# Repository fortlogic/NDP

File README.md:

# [NDP][]

Thanks for starting a project with Haskeleton! If you haven't heard of it
before, I suggest reading the introductory blog post. You can find it here:
<http://taylor.fausak.me/2014/03/04/haskeleton-a-haskell-project-skeleton/>.

Before you get started, there are a few things that this template couldn't
provide for you. You should:

-   Add a synopsis to `package.yaml`. It should be a short (one sentence)
    explanation of your project.

-   Add a description to `package.yaml`. This can be whatever you want it to
    be.

-   Add a category to `package.yaml`. A list of categories is available on
    Hackage at <http://hackage.haskell.org/packages>.

-   Rename `library/Example.hs` to whatever you want your top-level module to
    be called. Typically this is the same as your package name but in
    `CamelCase` instead of `kebab-case`.

    -   Don't forget to rename the reference to it in
        `executable/Main.hs`!

-   If you are on an older version of Stack (<1.0.4), delete `package.yaml` and
    remove `/*.cabal` from your `.gitignore`.

Once you've done that, start working on your project with the Stack commands
you know and love.

``` sh
# Build the project.
stack build

# Run the test suite.
stack test

# Run the benchmarks.
stack bench

# Generate documentation.
stack haddock
```

Thanks again, and happy hacking!

[NDP]: https://github.com/githubuser/NDP

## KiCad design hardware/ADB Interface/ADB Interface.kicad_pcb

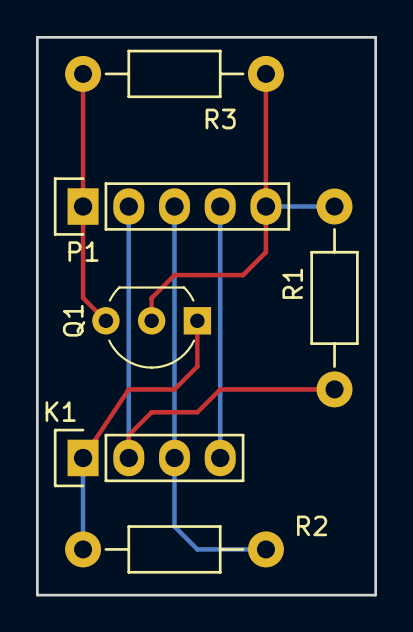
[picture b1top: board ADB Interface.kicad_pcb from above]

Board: 2 copper layers, 18.8 x 31.0 mm, 6 parts (0 on the bottom side), 6 nets.

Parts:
K1: ADB; Socket_Strip_Straight_1x04
P1: CONN_01X05; Socket_Strip_Straight_1x05
Q1: ZVNL110A; TO-92_Inline_Wide
R1, R2, R3: 470; Resistor_Horizontal_RM10mm

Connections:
+3V3: P1.5, Q1.2, R1.1, R3.2
+5V: K1.3, P1.3, R2.2
/adb: P1.1, Q1.3, R3.1
/~poweron: K1.2, P1.2, R1.2
GND: K1.4, P1.4
unnamed: K1.1, Q1.1, R2.1

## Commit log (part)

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2016-09-23 Initial commit.
2016-09-23 Fixed TileROM.hs from writing inverted tiles into a ROM.
2016-09-24 Update cbm tileset to include all letters.
2016-09-28 Refactored build system.
2016-09-29 basic testing framework setup.
2016-09-29 Started TMDS encoder.
2016-10-02 Research folder contains papers and articles that I don't have the rights to post publicly. I might commit a list with titles and links if someone else wants them.
2016-10-02 TMDS data encoding complete, testing and control codes still unfinished.
2016-10-02 All but the reference TMDS tests fail.
2016-10-02 x(n)or encoding and decoding functions properly.
2016-10-03 Finished TMDS encoding.
2016-10-04 Fixed some language declarations, added some interesting bit shuffling routines.
2016-10-04 Reorganisation in progress.
2016-10-04 Make system builds.
2016-10-04 Reorganisation finished, tests work fine.
2016-10-04 Restructuring clash compilation to handle nested modules.
2016-10-05 Started writing timing code. I hate election season.
2016-10-05 Added arrow instance for signals. Some arrow laws have been shown to be correct, others will be proven when time permits.
2016-10-06 Changed some names, added some module exports, added C64 inspired colour palette.
2016-10-06 Modified TMDS to be a little more friendly, begun work on video signal generator, and defined some initial clock domains.
2016-10-06 RGB video generator theoretically works, needs to be hooked up to a serialiser.
2016-10-06 Renamed video generator, started using proper clock domains for pixel logic.
2016-10-07 Started putting together the pieces to form the HDMI signal generator.
2016-10-08 HDMI generator should theoretically be capable of synthesising a test image. Still need to hook it up to ODDR output elements and test it on the actual fpga first.
2016-10-08 copied over a vagrant file from another project.
2016-10-09 Teaching the build system about vagrant.
2016-10-09 withVagrant fails if the vagrant status oracle cannot startup the vm.
2016-10-10 Added oracle for CPU architecture.
2016-10-12 Build system is a little stricter in terms of what CLaSH files can be compiled into vhdl, but output is not properly segregated into separate containers.
2016-10-12 Added the default constraints file for the Pipstrello (v2) board.
2016-10-16 can build ghdl test benches.
2016-10-18 Correctly builds project file for the xilinx toolchain.
2016-10-22 Renamed research folder to reference, added ISE folder for storing Xilinx ISE project in a location that git won't track.
2016-10-22 Begun refactoring.
2016-10-22 Added bit file compilation.
2016-10-22 Finished refactor.
2016-11-02 Xilinx bit file generation seems to work.
2016-11-02 Added minimal vhdl DVI-D output test (from the lovely hamster works).
2016-11-02 Copied minimal dvi-d demo in preparation for integrating the TMDS encoder.
2016-11-02 cleanup.
2016-11-05 Fixed unnecessary recompilation of clash sources.
2016-11-05 tmds encoder test entity fully replicates the functionality of the minimal dvid test entity.
2016-11-08 tmds sort of works? the tv says ‘no signal’ most of the time but every few minutes displays several correct frames before the signal goes invalid again.
2016-11-08 Started separating top level (phony) targets into their own file.
2016-11-13 Rewrite encodeByte. TMDS encoding now works, MinimalDVIDPlusTMDS also works.
2017-01-04 Updated the tilemap to look prettier (unified the character weight).
2017-01-08 Made an ADB schematic and PCB layout.
    No idea if it’ll work. ;)
2017-01-08 Updated .gitignore.
2017-03-16 Futzed around with the hardware schematic.
2017-03-16 Started trying to implement an ADB bus.
2017-04-22 Updated to build with GHC-8.
2017-04-22 Project builds successfully.
2017-04-22 Bitfile for the HDMI test now builds successfully.
2017-05-05 Fixed various configuration bugs in the build system. Also started adding fpga related shortcuts to the build system.
2017-05-15 Added more shortcuts.
2017-05-15 Made constraint building (hopefully) more flexible.
2017-05-16 Added a top level fpga demo where all of the vhdl (aside from a small generic clock entity), and specifically the top level entity, is written entirely in Clash.
2017-05-16 stuff
2017-05-20 Added a vhdl package for talking to an SD card.
2017-05-20 Some cleanup.
2017-05-20 SDCard.vhdl works correctly in the xilinx ISE.
2017-05-20 Added SD card constraints.
2017-06-06 Created an SD card controller primitive that clash and the xilinx tools correctly synthesise.
2017-06-07 Made some changes in efforts to make it work with a real SD card. (hint: it doesn’t).
2018-03-27 Begun writing ALU
2018-03-27 Fixing build config.
2018-03-27 ALU faults are a thing.
    Once we have some
2018-04-02 Working on the ALU
2018-04-02 Restructured the ALU result type
2018-04-03 Added netlist ‘busses’
    specifying constraints is somewhat less horrific.
2018-04-05 Added wing A to constraints
    Right now it’s as a pullup. In the future the I/Oness and pullness of wing busses is something that should be specified in a designs Config.hs.
2018-04-06 Added other wings as constraints
2018-04-08 Added popcount ALU instruction
2018-04-08 Added some dependencies.
2018-04-08 Added PopCount test
2018-04-08 deleted cabal file
2018-04-10 Updated cabal deps
2018-04-10 Added PopCount vhdl entity
2018-04-10 Begun generalising HDL generation
    Start of support for more than just VHDL.
2018-04-10 Added verilog support
    breaks bitfile generation
2018-04-10 presence of XILINXROOT is now optional
2018-04-10 unbroke bitfile generation
2018-04-11 can now build fpga bitfiles from verilog
    yay!
2018-04-11 But I prefer vhdl :3
2018-04-23 Started thinking about how registers should work
2018-04-23 Royally fu… I mean moving stuff about.
2018-04-24 everything in `hardware/` seems to build…
2018-04-24 Everything builds
    But does it work? ;)
2018-04-24 We need a readme
    Right now it’s just TODOs, but we’ve got to start somewhere?
2018-04-24 Made Clash generation less crap.
2018-04-24 Added a todo
2018-04-24 Things mostly build
    Tests are still broken I think.
2018-04-24 Tests work
2018-04-24 Tests run
    oh god so many warnings.
2018-04-24 building stuff works again
    except for bitfiles :p
2018-04-24 Bitfile generation works
2018-04-24 forgot to depend on clash-ghc 😳
2018-04-24 Added fpga stage command
2018-04-25 bumped resolver
2018-04-25 Got Hamster’s Minimal DVID project to build
2018-04-25 Made VM a bit smaller
    Also reverted the pixel generator in HamsterMinimalDVID to the default.
2018-04-26 Renamed CLaSH to Clash
    Finally!
2018-04-26 Deleted template readme
2018-04-26 poked at the readme
2018-04-28 Updated TODOs
2018-05-02 Signals can be stretched
    needs documentation and tests.
2018-05-02 Shuffled stuff about
2018-05-07 PureClashTest generates vhdl
    Though the build system doesn’t build yet…
2018-05-07 Factored PureClashTest
    It now demonstrates the ability to have more than one synthesisable ‘top’ entity.
2018-05-11 `stack build` works
    Still lots of warnings though, and no guarentees that anything runs correctly.
2018-05-11 clash build shortcut works
2018-05-11 Added some textbook references
2018-05-11 Fixed some warnings
2018-05-11 Updated resolver.
2018-05-11 Fixed all the warnings
    almost :3
2018-05-11 primitive generation isn’t broken
2018-05-16 clash shortcut correctly builds everything
2018-05-18 Trying to get primitives to work properly.
    They don’t quite yet.
2018-05-18 Trying to get ghdl to work…
2018-05-18 Moved stuff about
2018-05-18 Fixing clockstrobe primitive
2018-05-18 clockStrobe# generates the right VHDL
    Note to self: check that the right VHDL actually runs…
2018-05-19 Working on GHDL invocation
    doesn’t work properly yet, also rearranged some config stuff.
2018-05-20 hdl library manifest is more helpful
    It just has a list of directory hashes and will someday help track which libraries were rebuilt?
2018-05-21 Working on GHDL
    In the meantime you can query clash for a list of projects and targets.
2018-08-12 Begun scaffolding tests for primitives
2018-08-13 Started a template haskell test harness for testing primitives.
2018-08-15 Fixed a lot of annoying warnings
    Focusing now mostly on the test suite being sane. Build system still needs to have proper GHDL stuff completed.
2018-08-16 Primitive testing TH is on somewhat firmer ground
2018-08-18 Commenting out verilog test stubs
2018-10-01 org-mode ftw
2018-10-01 updating resolver to lts-12.11
2018-10-01 just for fun
    gource is fun to play with.
2018-10-02 Moved dependency haskell repos from my ownership to fortlogic.
2018-10-04 removed md5 dependency.
2018-10-04 meaningless change
    made a todo comment less (or possibly more) obtuse.
2018-10-04 Another meaningless change
    because CI, thats why.
2018-10-04 added todo in readme
2018-10-05 Separating xilinx-primitives into their own branch.
2018-10-05 pruning non xilinx primitive stuff.
2018-10-05 Separated out vhdl primitives.
2018-10-05 Stripping out primitive stuff
    It’s not actually ready yet…
2018-10-05 fixing package.yaml
2018-10-05 still fixing package.yaml…
    -_-
2018-10-05 Moving tests about
    In the middle of rearranging how tests are structure, nothing works quite yet…
2018-10-05 Updating README.
2018-10-05 Move complete, I think
2018-10-09 meh…
2018-10-09 oh ffs
2018-10-11 Started making some diagrams
    oh god can you even diff omnigraffle? This is all gonna end in tears…
2018-10-11 Updated lts because why not.
2018-10-11 actually yeah, setup go byebye.
2018-10-11 setup and clean consistent w/other shortcuts
    Why is setup a thing again?
2018-10-11 why not?
2018-10-16 Add CI badge to show state of README.org.
2018-10-16 so I was drinking the other night and ended up setting my default shell to `tcsh`. Why not share the love?
    Also @jstoker, my gorgeous CI person, wants something pushed to develop so yolo I guess?
2018-10-16 renamed vanity
2018-10-17 just for fun
2018-10-18 Adding dependency
2018-10-18 Creating datatype to replace NDP.config
2018-10-18 Making datatypes compatible with Dhall.
2018-10-29 PopCountTest builds on clash 0.99
2018-10-29 HamsterMinimalDVID now builds on clash 0.99
    but does it work? that’s the question.
2018-10-29 MinimalDVIDPlusTMDS builds with clash 0.99
2018-10-29 remove SD card entity
    doesn’t need to exist yet.
2018-10-29 PrimitiveTest doesn’t belong on this branch yet
2018-11-02 Moved resources to build system
    constraint files and character ROM belong more to the build system than the hardware.
2018-11-02 Added shortcut for building character rom
    building everything but a bitfile seems to work fine.
2018-11-02 moving rom sources to their own top level directory.
2018-11-04 Sketching out dhall character rom
2018-11-06 changing the character rom schema a bit.
2018-11-07 Moving Make.Command into Make.Shortcuts.
2018-11-12 Correctly parsing verbosity flags.
2018-11-12 CLI is starting to take shape.
2018-11-26 updating lts.
2018-11-30 well thats just embarrasing
2018-12-05 Fixed some vagrant and xflow related stuff
2018-12-06 Added dhall file normaliser shortcut
2018-12-06 Renaming some entities
2018-12-06 Projects are a thing that can be parsed
2018-12-06 Projects oracle is a thing
2018-12-06 renamed project fields, added some helpers.
2018-12-06 Parsing commands is starting to make more sense.
2018-12-07 Splitting commands into separate files
2018-12-07 Clean command
    now to start actually doing stuff with these commands…
2018-12-14 Moving stuff around a bit.
2019-10-22 Added a crappy front panel
2019-11-02 Updated stack and lts
    stack-2.1.3
    lts-12.26
2019-11-02 stack run works
    also bumped lts
2019-11-02 Separating synthesis domains
    Template Haskell doesn’t seem to like having a domain be defined in the same file that the domain it’s derived from is defined.
2019-11-02 Bumped to clash-1.0.1
    Still have fires to put out.
2019-11-02 ndp library builds successfully
    executable is still broken, and entities haven’t been updated.
